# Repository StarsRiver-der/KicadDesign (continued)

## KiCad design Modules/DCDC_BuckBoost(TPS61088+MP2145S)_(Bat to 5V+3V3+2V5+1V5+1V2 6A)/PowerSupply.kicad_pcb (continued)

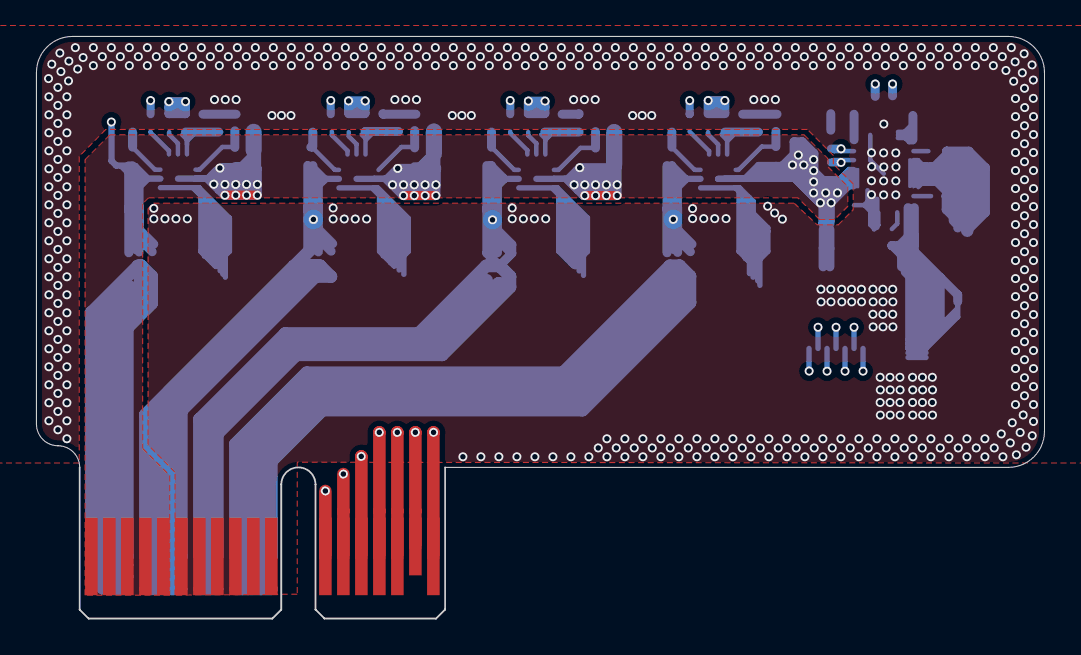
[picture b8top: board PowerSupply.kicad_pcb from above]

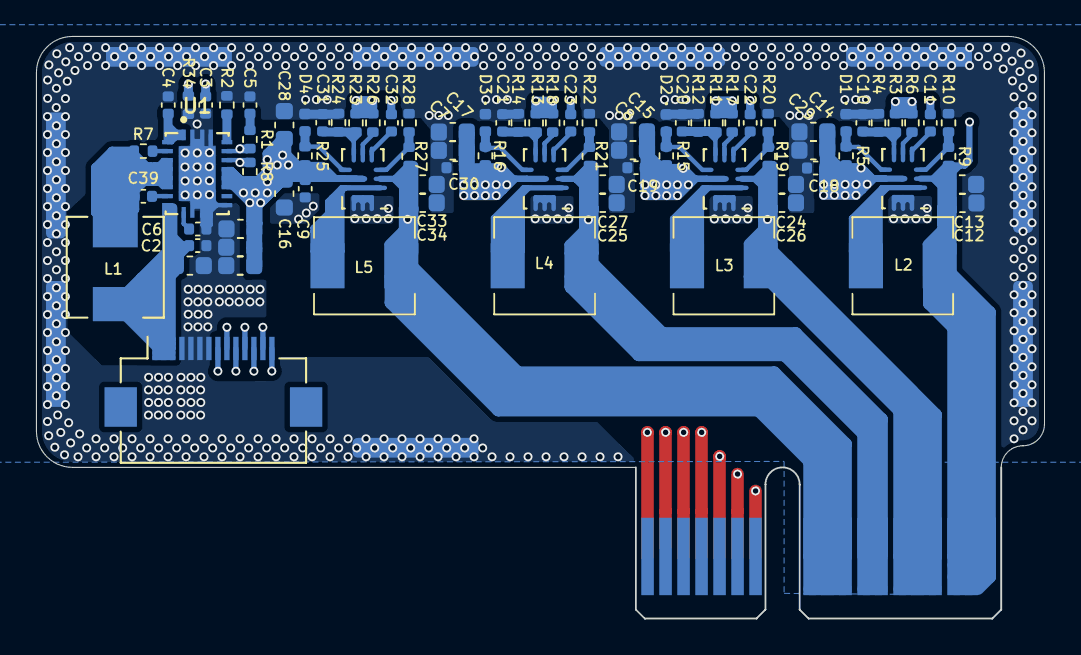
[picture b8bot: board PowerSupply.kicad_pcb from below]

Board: 4 copper layers, 56.0 x 32.3 mm, 92 parts (91 on the bottom side), 47 nets.

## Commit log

2021-04-23 update DCDC_BatCharger
2021-04-23 new set files
2021-04-23 add Module DCDC_Boost(LM51571-Q1)_(3v-13v to 24v 0.3A)
2021-04-24 update modules
2021-05-05 add LDO_BatCharger_(USB-4.2v 0.54A)
2021-05-05 update LDO_BatCharger_(USB-4.2v 0.54A)
2021-05-18 add readme
2021-09-26 need mor work
2021-10-03 add new modules
2021-10-03 test
2021-10-03 Update 23
2021-10-03 test delete
2021-10-06 detail fix
2021-10-07 add an precision amplifier design
2021-10-08 Replace Dual-Power.kicad_pcb
2021-10-08 add manual
2021-10-08 cache created
2021-10-12 design fix
2021-10-13 update kicad editor version
2021-10-23 update dcdc_stepdown(LTC3892)
2021-10-25 update Dual-power
2021-10-31 update dual_power
2021-10-31 update Dual-Power design parameter
2021-11-06 update WirelessPower.sch (fix resistance value)
2021-11-07 update WirelessPower PCB LAYOUT
2021-11-07 update WirelessPower.sch by kicad6
2021-11-07 add lost files
2021-11-12 update WirelessPower layout
2021-11-12 fix old version file
2021-11-17 update PowerSupply(in Kicad6)
2021-11-21 do rename
2021-11-21 Gerber Files create in old version
2021-11-28 add new wirelesspower desigh: P40
2021-11-28 wirelesspowerP40 io fix
2021-12-12 WirelessPowerP40_Transmitter update
2021-12-14 update Dual-Power components value
2021-12-14 add simple cooler controller for WirelessPowerTransmitter P40
2021-12-15 change WirelessPowerTransmitter P40 usb connector
2021-12-16 Outshape optimization of WirelessPowerTransmitterP40
2021-12-16 fix description in Dual-Power.kicad_sch
2021-12-16 bom update
2021-12-16 add bom
2021-12-16 Wrong Silk text fix
2021-12-16 update bom
2021-12-17 Remess WirelessPowerP40
2021-12-17 change TS80003 INTv ripple suppression indoctor form 600 to 1uH
2021-12-18 WirelessPowerP40_Transmitter optimization
2021-12-18 add drill map file for WirelessPowerP40_Transmitter
2021-12-19 replace low Vr diode BAT54 with BAS101s in WirelessPowerP40_Transmitter
2021-12-19 do nothing
2021-12-19 continue..
2021-12-20 add PD(19V3A) support for WirelessPowerP40_Transmitter
2021-12-20 DCDC_StepDown(TLC3892) > fix capacity value
2021-12-21 WirelessPowerP40_Transmitter > change D3 value with pacific diode
2021-12-27 continuing...
2022-01-01 finished WirelessPowerP40_Receiver
2022-01-02 fix routing
2022-01-04 fix footprint of 74lvc
2022-01-04 replace USB Connector
2022-01-05 update USB-Type-C,with QC support
2022-01-06 add hotpad
2022-01-11 rollback (PD3.0 fix)
2022-01-11 update hotpad
2022-01-12 add programing app
2022-01-12 add new-version UserGuide
2022-01-12 add WirelessPowerGui_setup program
2022-01-13 IO silk label fix
2022-01-13 re-saved by kicad6
2022-01-13 fix fatal error
2022-01-19 sch prettify
2022-02-20 add new prj
2022-02-21 finish prj USB3G2_SATA3_Bridge(JMS580)
2022-02-21 Fix USB3G2_SATA3_Bridge(JMS580) 1AM Pinout
2022-02-21 Add Datasheet for USB3G2_SATA3_Bridge(JMS580)
2022-02-23 Symbol Value unified
2022-02-26 Revert "delete WirelessPowerGUI"
2022-02-26 Path fix on JMMassProd.ini
2022-02-26 Add Preview
2022-02-28 Add FOD tech user guide
2022-03-03 USB3G2_SATA3_Bridge(JMS580) Error Fix (USB3.0 TX RX Swap problem)
2022-03-04 USB3G2_SATA3_Bridge(JMS580) Copper refill
2022-03-04 Fix layout
2022-03-12 Update .gitignore rule (DO NOT SAVE .PRL)
2022-03-12 Update .gitignore rule fix (DO NOT SAVE .PRL)
2022-03-14 Update description in Sch
2022-03-24 Add GuideLine of High-Speed Layout
2022-03-25 Sort Out
2022-03-25 State Update
2022-03-27 Update USB2_Jtag_Bridge
2022-03-30 Finish USB2_Jtag_Bridge
2022-03-30 Opt for preview.jpg path
2022-03-30 Crystal footprint fix
2022-04-01 New design initialized
2022-04-06 Remove PCBsch useless layers
2022-04-08 Initialization of XC6SLX25(FTG256)_CoreBoard
2022-04-15 Update XC6SLX25(FTG256)_CoreBoard
2022-04-19 Update XC6SLX25(FTG256)_CoreBoard (DDR3 Routing)
2022-04-22 Update XC6SLX25(FTG256)_CoreBoard (FPGA Routing)
2022-04-24 Update FPGA_XC6SLX25_CoreBoard
2022-04-26 Finish XC6SLX25(FTG256)_CoreBoard (review & check is needed)
2022-04-26 XC6SLX25(FTG256)_CoreBoard Checked
2022-04-26 FPGA_XC6SLX25_CoreBoard optimize
2022-04-27 XC6SLX25(FTG256)_CoreBoard increase 3V3,2V5 power output ability
2022-04-27 add XC6SLX25(FTG256)_BaseBoard_OnlyIO
2022-04-27 update FPGA_XC6SLX25_BaseBoard_OnlyIO
2022-04-28 finish XC6SLX25(FTG256)_BaseBoard_OnlyIO (sample)
2022-04-29 FPGA_XC6SLX25_CoreBoard optimize (FIN)
2022-05-02 clean FPGA_XC6SLX25_CoreBoard
2022-05-04 add UG
2022-05-09 replace ArrayResistence(x2) with x4
2022-05-17 add Shell Design
2022-07-03 update Stack Structure
2022-07-06 update naming rule
2022-07-07 update ESP module
2022-07-11 update ESP Wrover module
2022-07-12 add ESP-S3-WROOM2 module
2022-07-12 update ESP-S2-Wrover module
2022-07-13 update 3d modules
2022-07-14 update ESP32 modules
2022-07-15 add 3D diagram
2022-07-17 update ESP32_S2_WROVER_EVB screen layout
2022-07-19 add petalinux-tools-reference-guide.pdf
2022-07-20 add 3D module for ESP32_S2_WROVER_EVB
2022-07-20 update ESP32_S2_WROVER_EVB
2022-07-20 update ESP32_S2_WROVER_EVB 3D View
